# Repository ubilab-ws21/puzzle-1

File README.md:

# Divert power to machine room door (puzzle-1)
This puzzle is the first part of the 2021 ESCLAB.
According to that orange american man that once was US president, it's the best puzzle the world has ever seen.

## Objective
Divert the emergency power to the door that prevents you fom entering the second room.

## Story
There is some wiring on the wall. When you'll find some more panels to create the connection maybe you can divert the power to the door. Apparently the emergency power has not been used in ages.  
  
You spot a cube on the table in the room thats sides look like panels that yould be used for that.  
  
Upon further inspection you see that the cube starts sparkling when moving it in the hand. Also there are weird symbols on each side.  
Also in the room there is some kind of comic, that has the symbols in the title and a hint "to the sun".  
Maybe placing the cube with the symbols of the comic towards the sun (top) in the correct order it will open.

After finishing the sequence the cube lights up greeen and suddenly the panels will unlatch so you can take 'em off.  
You solve the wire-maze, given by the panels and place them so the connection between "emergency power" and the keypad is created on the wall.  

The door opens and you step into the next room.

And then you die. Or maybe something nicer happens - that's up to the people doing the next puzzles. :)

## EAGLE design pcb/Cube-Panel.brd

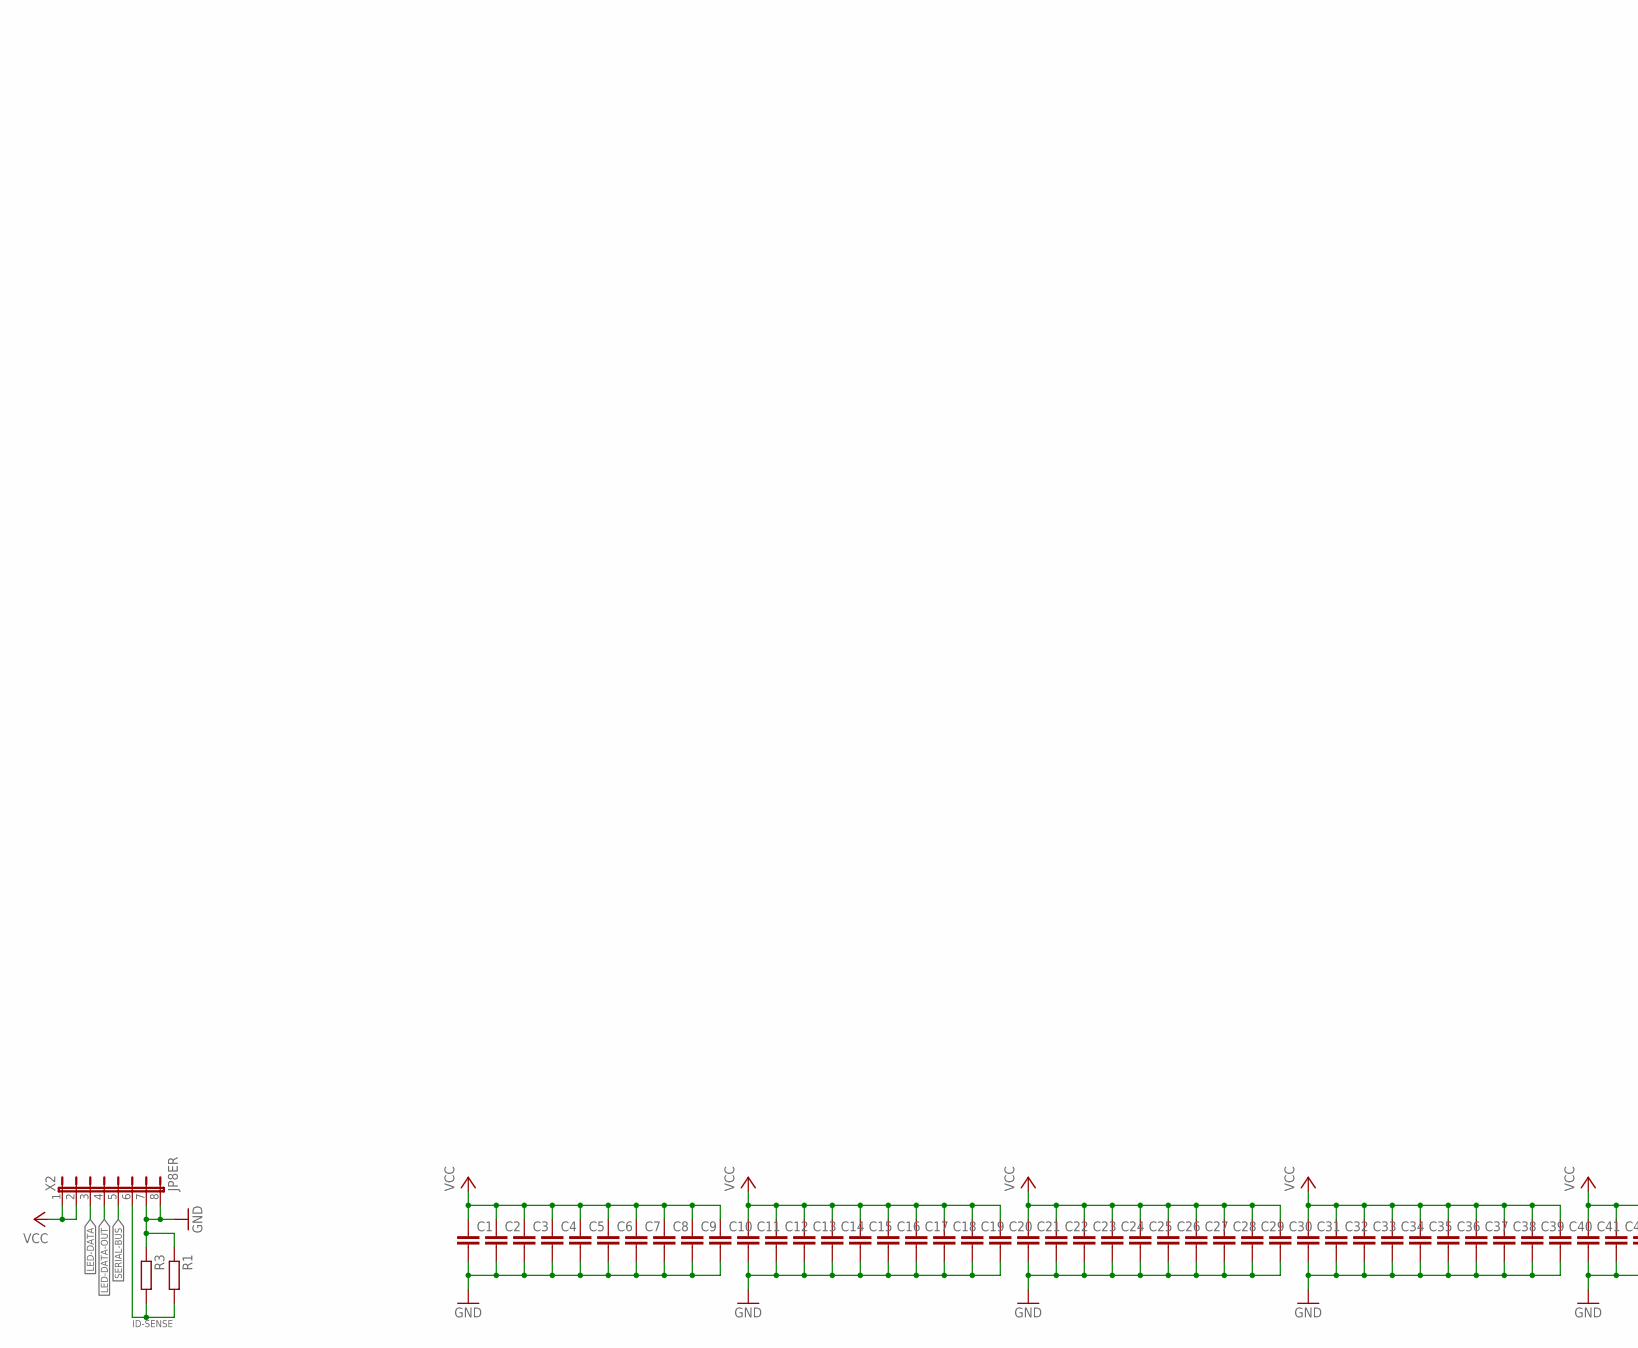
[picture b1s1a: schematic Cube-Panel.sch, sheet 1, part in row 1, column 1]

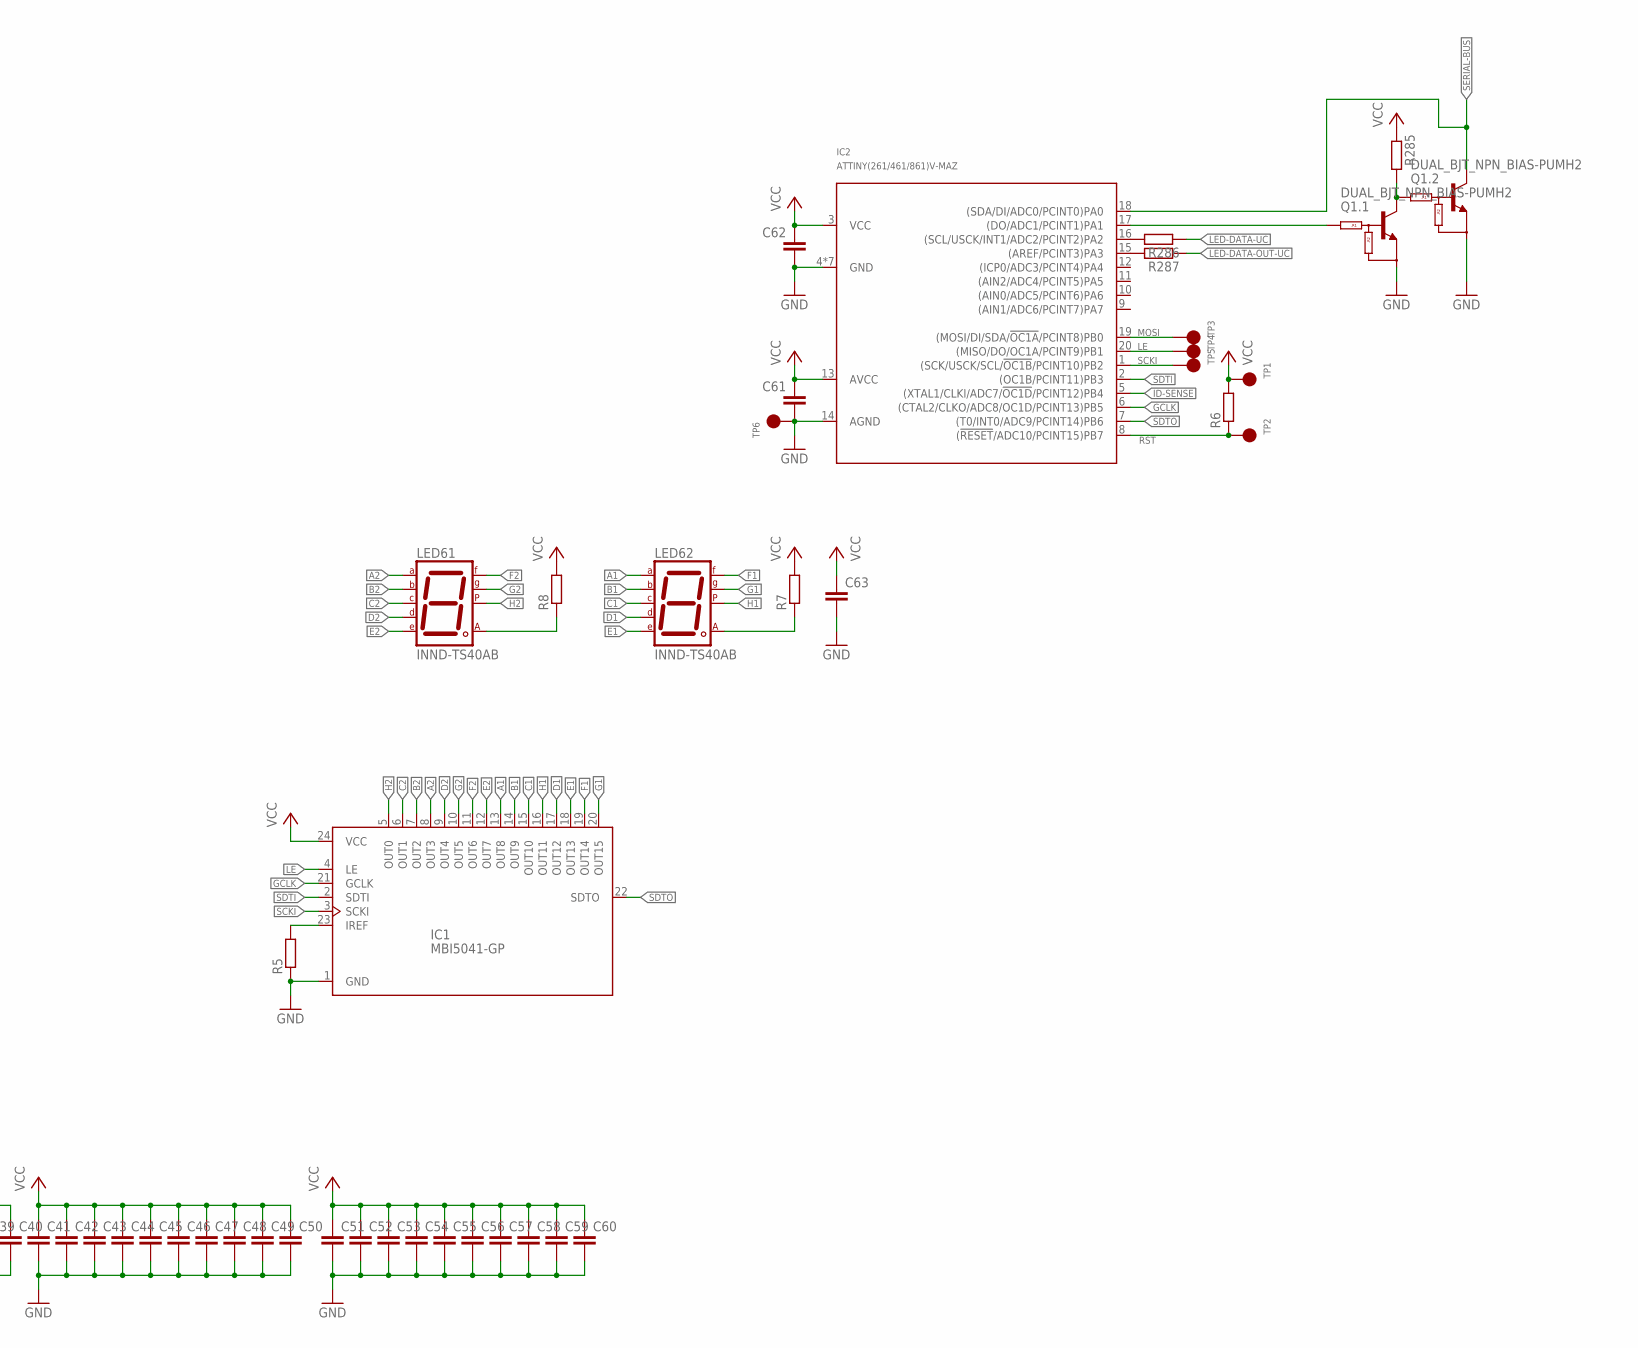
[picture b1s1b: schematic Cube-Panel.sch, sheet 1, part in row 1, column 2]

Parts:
C1, C2, C3, C4, C5, C6, C7, C8, C9, C10, C11, C12, C13, C14, C15, C16, C17, C18, C19, C20, C21, C22, C23, C24, C25, C26, C27, C28, C29, C30, C31, C32, C33, C34, C35, C36, C37, C38, C39, C40, C41, C42, C43, C44, C45, C46, C47, C48, C49, C50, C51, C52, C53, C54, C55, C56, C57, C58, C59, C60, C61, C62, C63: KONDENSATOR-0603; 0603
IC1: MBI5041-GP; SSOP24-150-0.635
IC2: ATTINY(261/461/861)V-MAZ; QFN-20
LED61, LED62: INND-TS40AB; 7SEG-13
Q1: DUAL_BJT_NPN_BIAS-PUMH2; SOT-363(SC-88)
R1, R3, R5, R6, R7, R8, R285, R286, R287: WIDERSTAND-0603; 0603
TP1, TP2, TP3, TP4, TP5, TP6: TP; TP[1.5][R]
X2: JP8ER; JP8

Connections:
A1: IC1.13 (OUT8), LED62.10 (A)
A2: IC1.8 (OUT3), LED61.10 (A)
B1: IC1.14 (OUT9), LED62.9 (B)
B2: IC1.7 (OUT2), LED61.9 (B)
C1: IC1.15 (OUT10), LED62.8 (C)
C2: IC1.6 (OUT1), LED61.8 (C)
D1: IC1.17 (OUT12), LED62.5 (D)
D2: IC1.9 (OUT4), LED61.5 (D)
E1: IC1.18 (OUT13), LED62.1 (E)
E2: IC1.12 (OUT7), LED61.1 (E)
F1: IC1.19 (OUT14), LED62.2 (F)
F2: IC1.11 (OUT6), LED61.2 (F)
G1: IC1.20 (OUT15), LED62.3 (G)
G2: IC1.10 (OUT5), LED61.3 (G)
GCLK: IC1.21 (GCLK), IC2.6 ((CTAL2/CLKO/ADC8/OC1D/PCINT13)PB5)
GND: C1.P$2 (2), C2.P$2 (2), C3.P$2 (2), C4.P$2 (2), C5.P$2 (2), C6.P$2 (2), C7.P$2 (2), C8.P$2 (2), C9.P$2 (2), C10.P$2 (2), C11.P$2 (2), C12.P$2 (2), C13.P$2 (2), C14.P$2 (2), C15.P$2 (2), C16.P$2 (2), C17.P$2 (2), C18.P$2 (2), C19.P$2 (2), C20.P$2 (2), C21.P$2 (2), C22.P$2 (2), C23.P$2 (2), C24.P$2 (2), C25.P$2 (2), C26.P$2 (2), C27.P$2 (2), C28.P$2 (2), C29.P$2 (2), C30.P$2 (2), C31.P$2 (2), C32.P$2 (2), C33.P$2 (2), C34.P$2 (2), C35.P$2 (2), C36.P$2 (2), C37.P$2 (2), C38.P$2 (2), C39.P$2 (2), C40.P$2 (2), C41.P$2 (2), C42.P$2 (2), C43.P$2 (2), C44.P$2 (2), C45.P$2 (2), C46.P$2 (2), C47.P$2 (2), C48.P$2 (2), C49.P$2 (2), C50.P$2 (2), C51.P$2 (2), C52.P$2 (2), C53.P$2 (2), C54.P$2 (2), C55.P$2 (2), C56.P$2 (2), C57.P$2 (2), C58.P$2 (2), C59.P$2 (2), C60.P$2 (2), C61.P$2 (2), C62.P$2 (2), C63.P$2 (2), IC1.1 (GND), IC2.4 (GND), IC2.14 (AGND), IC2.PAD (GND), IC2.PAD$1 (GND), IC2.PAD$2 (GND), IC2.PAD$3 (GND), IC2.PAD$4 (GND), IC2.PAD$5 (GND), Q1.1 (E), Q1.4 (E), R1.P$1 (1), R3.P$1 (1), R5.P$1 (1), TP6.P$1, X2.7, X2.8; also elsewhere on the board
H1: IC1.16 (OUT11), LED62.7 (DP)
H2: IC1.5 (OUT0), LED61.7 (DP)
ID-SENSE: IC2.5 ((XTAL1/CLKI/ADC7/!OC1D!/PCINT12)PB4), R1.P$2 (2), R3.P$2 (2), X2.6
LE: IC1.4 (LE), IC2.20 ((MISO/DO/OC1A/PCINT9)PB1), TP4.P$1
LED-DATA: X2.3; also elsewhere on the board
LED-DATA-OUT: X2.4; also elsewhere on the board
LED-DATA-OUT-UC: R287.P$1 (1); also elsewhere on the board
LED-DATA-UC: R286.P$1 (1); also elsewhere on the board
MOSI: IC2.19 ((MOSI/DI/SDA/!OC1A!/PCINT8)PB0), TP3.P$1
unnamed: IC1.23 (IREF), R5.P$2 (2)
unnamed: IC2.16 ((SCL/USCK/INT1/ADC2/PCINT2)PA2), R286.P$2 (2)
unnamed: Q1.5 (B), Q1.6 (C), R285.P$2 (2)
unnamed: IC2.15 ((AREF/PCINT3)PA3), R287.P$2 (2)
unnamed: LED61.6 (CA2), R8.P$1 (1)
unnamed: LED62.6 (CA2), R7.P$1 (1)
RST: IC2.8 ((!RESET!/ADC10/PCINT15)PB7), R6.P$1 (1), TP2.P$1
SCKI: IC1.3 (SCKI), IC2.1 ((SCK/USCK/SCL/!OC1B!/PCINT10)PB2), TP5.P$1
SDTI: IC1.2 (SDTI), IC2.2 ((OC1B/PCINT11)PB3)
SDTO: IC1.22 (SDTO), IC2.7 ((T0/INT0/ADC9/PCINT14)PB6)
SERIAL-BUS: IC2.18 ((SDA/DI/ADC0/PCINT0)PA0), Q1.3 (C), X2.5
SERIAL-BUS-TX: IC2.17 ((DO/ADC1/PCINT1)PA1), Q1.2 (B)
VCC: C1.P$1 (1), C2.P$1 (1), C3.P$1 (1), C4.P$1 (1), C5.P$1 (1), C6.P$1 (1), C7.P$1 (1), C8.P$1 (1), C9.P$1 (1), C10.P$1 (1), C11.P$1 (1), C12.P$1 (1), C13.P$1 (1), C14.P$1 (1), C15.P$1 (1), C16.P$1 (1), C17.P$1 (1), C18.P$1 (1), C19.P$1 (1), C20.P$1 (1), C21.P$1 (1), C22.P$1 (1), C23.P$1 (1), C24.P$1 (1), C25.P$1 (1), C26.P$1 (1), C27.P$1 (1), C28.P$1 (1), C29.P$1 (1), C30.P$1 (1), C31.P$1 (1), C32.P$1 (1), C33.P$1 (1), C34.P$1 (1), C35.P$1 (1), C36.P$1 (1), C37.P$1 (1), C38.P$1 (1), C39.P$1 (1), C40.P$1 (1), C41.P$1 (1), C42.P$1 (1), C43.P$1 (1), C44.P$1 (1), C45.P$1 (1), C46.P$1 (1), C47.P$1 (1), C48.P$1 (1), C49.P$1 (1), C50.P$1 (1), C51.P$1 (1), C52.P$1 (1), C53.P$1 (1), C54.P$1 (1), C55.P$1 (1), C56.P$1 (1), C57.P$1 (1), C58.P$1 (1), C59.P$1 (1), C60.P$1 (1), C61.P$1 (1), C62.P$1 (1), C63.P$1 (1), IC1.24 (VCC), IC2.3 (VCC), IC2.13 (AVCC), R6.P$2 (2), R7.P$2 (2), R8.P$2 (2), R285.P$1 (1), TP1.P$1, X2.1, X2.2; also elsewhere on the board

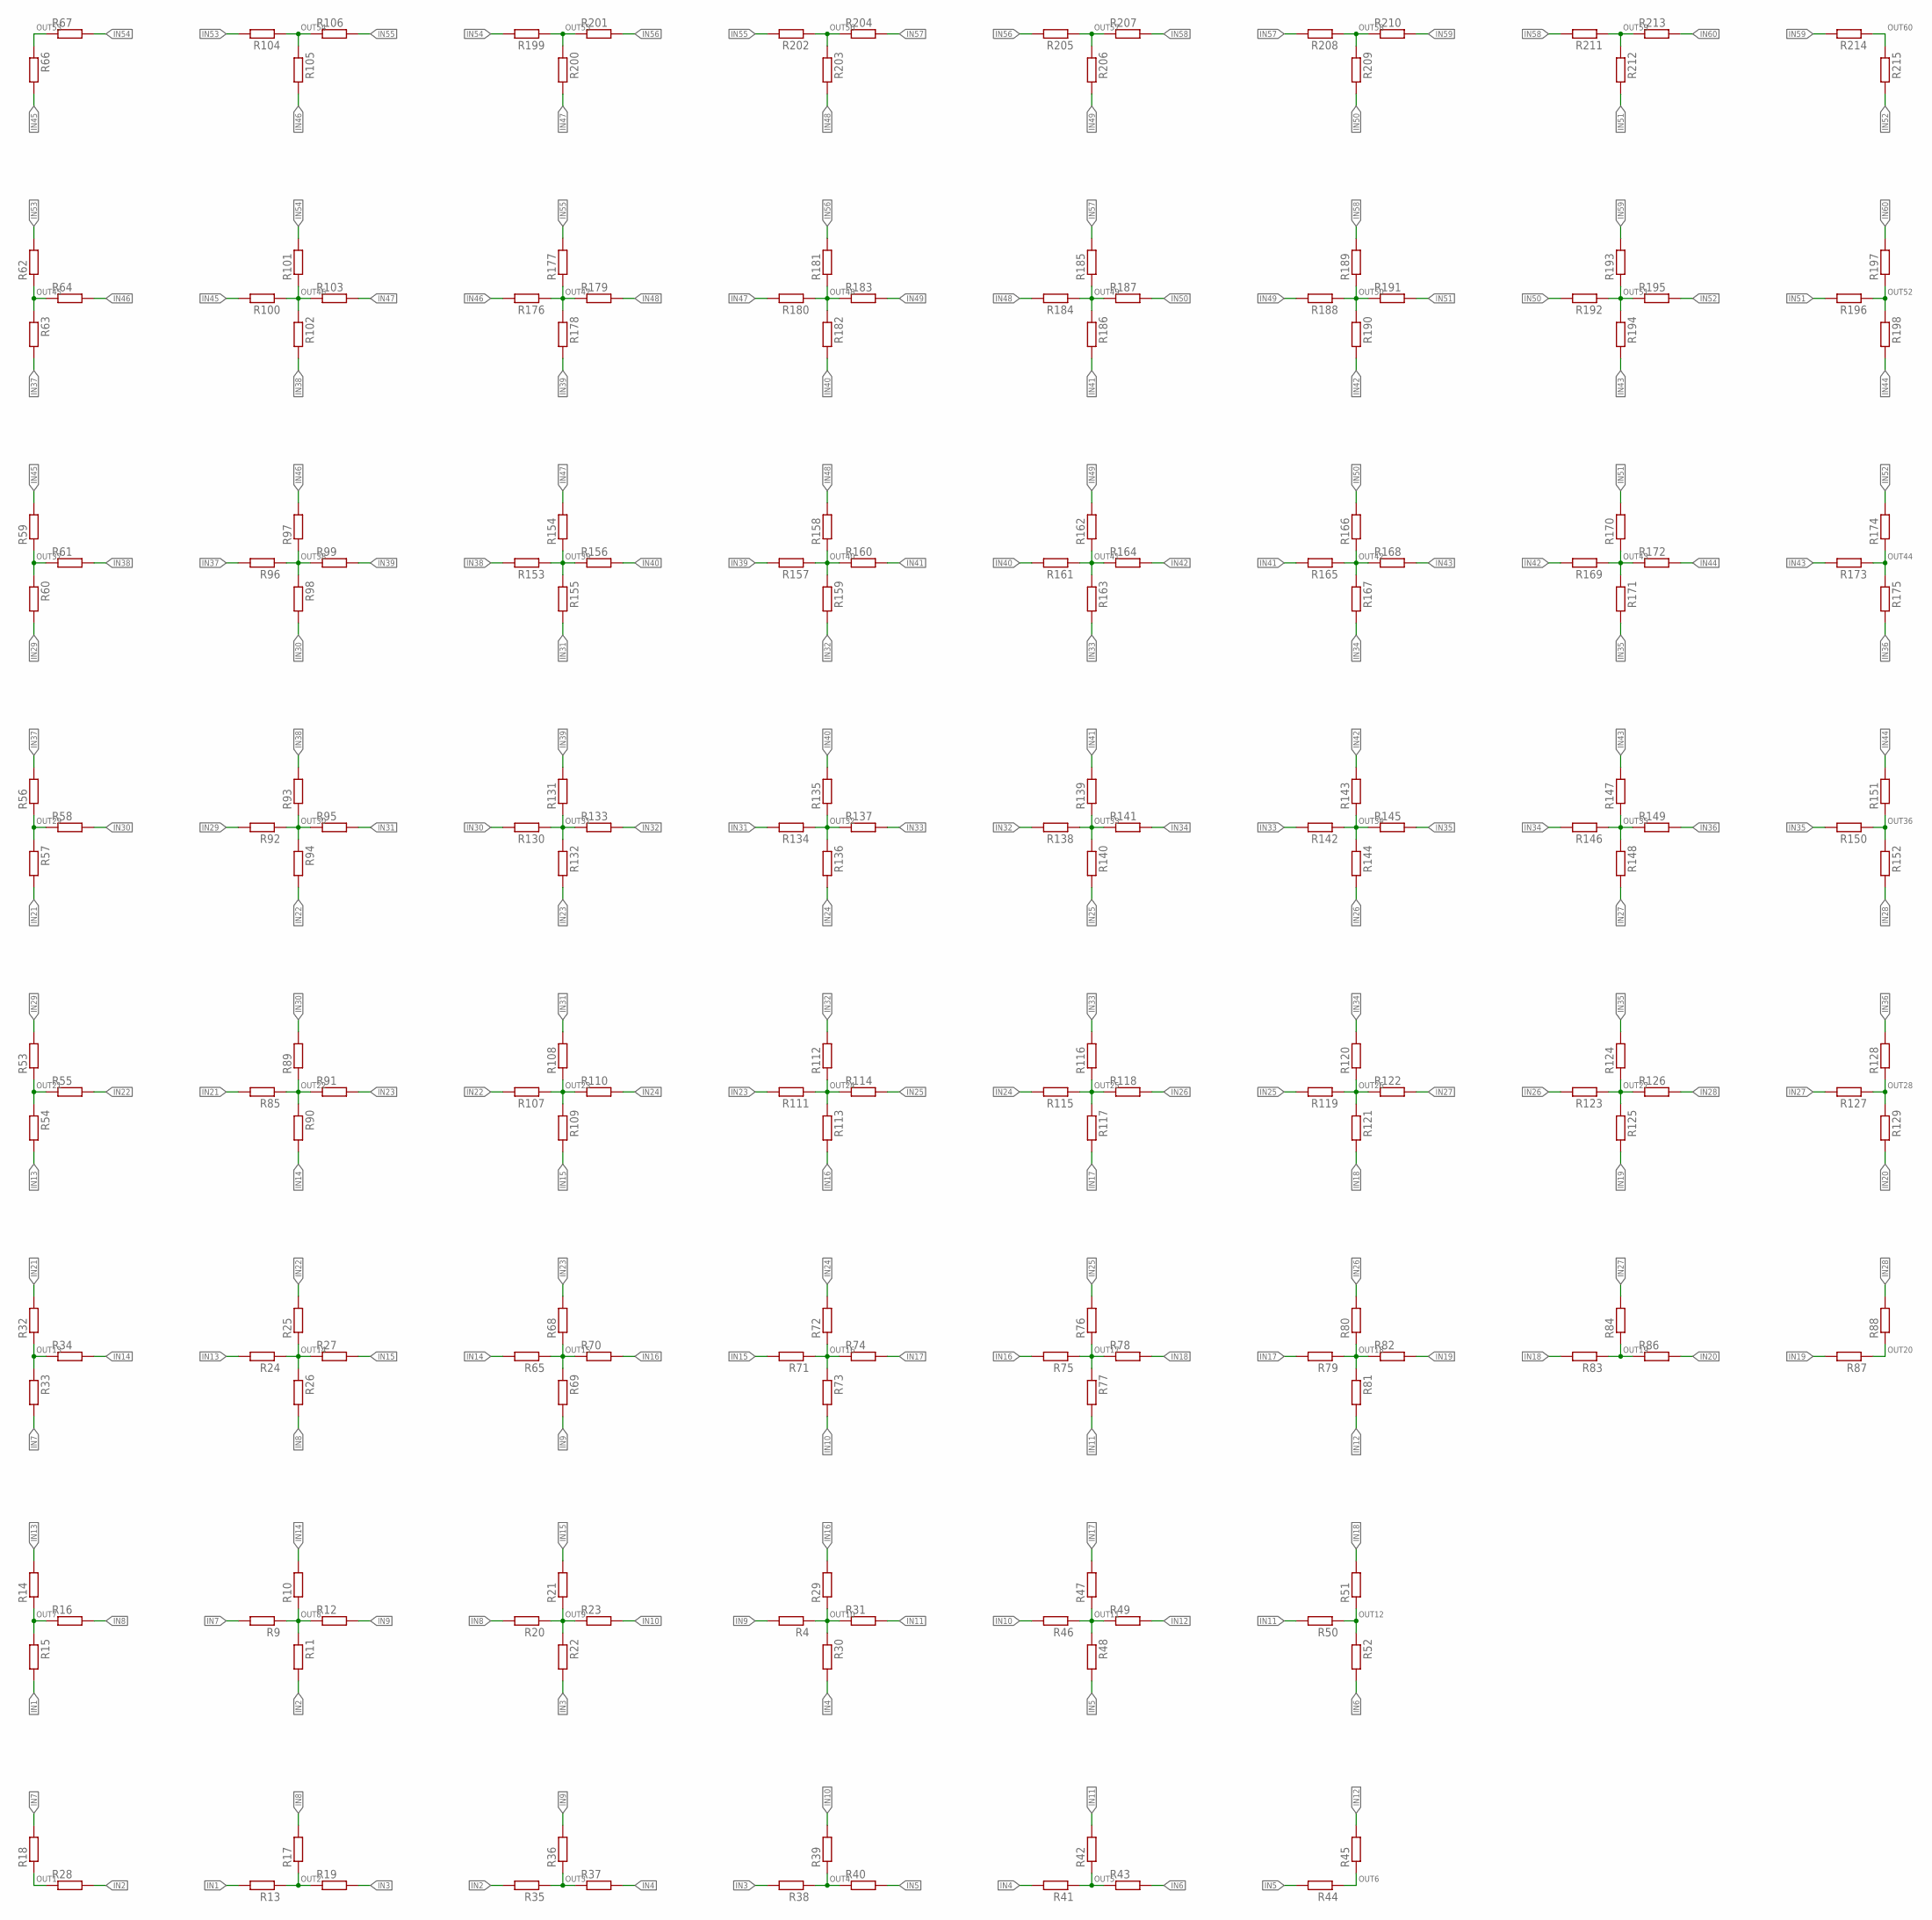
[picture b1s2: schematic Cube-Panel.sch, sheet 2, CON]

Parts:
R4, R9, R10, R11, R12, R13, R14, R15, R16, R17, R18, R19, R20, R21, R22, R23, R24, R25, R26, R27, R28, R29, R30, R31, R32, R33, R34, R35, R36, R37, R38, R39, R40, R41, R42, R43, R44, R45, R46, R47, R48, R49, R50, R51, R52, R53, R54, R55, R56, R57, R58, R59, R60, R61, R62, R63, R64, R65, R66, R67, R68, R69, R70, R71, R72, R73, R74, R75, R76, R77, R78, R79, R80, R81, R82, R83, R84, R85, R86, R87, R88, R89, R90, R91, R92, R93, R94, R95, R96, R97, R98, R99, R100, R101, R102, R103, R104, R105, R106, R107, R108, R109, R110, R111, R112, R113, R114, R115, R116, R117, R118, R119, R120, R121, R122, R123, R124, R125, R126, R127, R128, R129, R130, R131, R132, R133, R134, R135, R136, R137, R138, R139, R140, R141, R142, R143, R144, R145, R146, R147, R148, R149, R150, R151, R152, R153, R154, R155, R156, R157, R158, R159, R160, R161, R162, R163, R164, R165, R166, R167, R168, R169, R170, R171, R172, R173, R174, R175, R176, R177, R178, R179, R180, R181, R182, R183, R184, R185, R186, R187, R188, R189, R190, R191, R192, R193, R194, R195, R196, R197, R198, R199, R200, R201, R202, R203, R204, R205, R206, R207, R208, R209, R210, R211, R212, R213, R214, R215: WIDERSTAND-0603; 0603

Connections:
IN1: R13.P$2 (2), R15.P$2 (2); also elsewhere on the board
IN2: R11.P$2 (2), R28.P$2 (2), R35.P$2 (2); also elsewhere on the board
IN3: R19.P$2 (2), R22.P$2 (2), R38.P$2 (2); also elsewhere on the board
IN4: R30.P$2 (2), R37.P$2 (2), R41.P$2 (2); also elsewhere on the board
IN5: R40.P$2 (2), R44.P$2 (2), R48.P$2 (2); also elsewhere on the board
IN6: R43.P$2 (2), R52.P$2 (2); also elsewhere on the board
IN7: R9.P$2 (2), R18.P$2 (2), R33.P$2 (2); also elsewhere on the board
IN8: R16.P$2 (2), R17.P$2 (2), R20.P$2 (2), R26.P$2 (2); also elsewhere on the board
IN9: R4.P$2 (2), R12.P$2 (2), R36.P$2 (2), R69.P$2 (2); also elsewhere on the board
IN10: R23.P$2 (2), R39.P$2 (2), R46.P$2 (2), R73.P$2 (2); also elsewhere on the board
IN11: R31.P$2 (2), R42.P$2 (2), R50.P$2 (2), R77.P$2 (2); also elsewhere on the board
IN12: R45.P$2 (2), R49.P$2 (2), R81.P$2 (2); also elsewhere on the board
IN13: R14.P$2 (2), R24.P$2 (2), R54.P$2 (2); also elsewhere on the board
IN14: R10.P$2 (2), R34.P$2 (2), R65.P$2 (2), R90.P$2 (2); also elsewhere on the board
IN15: R21.P$2 (2), R27.P$2 (2), R71.P$2 (2), R109.P$2 (2); also elsewhere on the board
IN16: R29.P$2 (2), R70.P$2 (2), R75.P$2 (2), R113.P$2 (2); also elsewhere on the board
IN17: R47.P$2 (2), R74.P$2 (2), R79.P$2 (2), R117.P$2 (2); also elsewhere on the board
IN18: R51.P$2 (2), R78.P$2 (2), R83.P$2 (2), R121.P$2 (2); also elsewhere on the board
IN19: R82.P$2 (2), R87.P$2 (2), R125.P$2 (2); also elsewhere on the board
IN20: R86.P$2 (2), R129.P$2 (2); also elsewhere on the board
IN21: R32.P$2 (2), R57.P$2 (2), R85.P$2 (2); also elsewhere on the board
IN22: R25.P$2 (2), R55.P$2 (2), R94.P$2 (2), R107.P$2 (2); also elsewhere on the board
IN23: R68.P$2 (2), R91.P$2 (2), R111.P$2 (2), R132.P$2 (2); also elsewhere on the board
IN24: R72.P$2 (2), R110.P$2 (2), R115.P$2 (2), R136.P$2 (2); also elsewhere on the board
IN25: R76.P$2 (2), R114.P$2 (2), R119.P$2 (2), R140.P$2 (2); also elsewhere on the board
IN26: R80.P$2 (2), R118.P$2 (2), R123.P$2 (2), R144.P$2 (2); also elsewhere on the board
IN27: R84.P$2 (2), R122.P$2 (2), R127.P$2 (2), R148.P$2 (2); also elsewhere on the board
IN28: R88.P$2 (2), R126.P$2 (2), R152.P$2 (2); also elsewhere on the board
IN29: R53.P$2 (2), R60.P$2 (2), R92.P$2 (2); also elsewhere on the board
IN30: R58.P$2 (2), R89.P$2 (2), R98.P$2 (2), R130.P$2 (2); also elsewhere on the board
IN31: R95.P$2 (2), R108.P$2 (2), R134.P$2 (2), R155.P$2 (2); also elsewhere on the board
IN32: R112.P$2 (2), R133.P$2 (2), R138.P$2 (2), R159.P$2 (2); also elsewhere on the board
IN33: R116.P$2 (2), R137.P$2 (2), R142.P$2 (2), R163.P$2 (2); also elsewhere on the board
IN34: R120.P$2 (2), R141.P$2 (2), R146.P$2 (2), R167.P$2 (2); also elsewhere on the board
IN35: R124.P$2 (2), R145.P$2 (2), R150.P$2 (2), R171.P$2 (2); also elsewhere on the board
IN36: R128.P$2 (2), R149.P$2 (2), R175.P$2 (2); also elsewhere on the board
IN37: R56.P$2 (2), R63.P$2 (2), R96.P$2 (2); also elsewhere on the board
IN38: R61.P$2 (2), R93.P$2 (2), R102.P$2 (2), R153.P$2 (2); also elsewhere on the board
IN39: R99.P$2 (2), R131.P$2 (2), R157.P$2 (2), R178.P$2 (2); also elsewhere on the board
IN40: R135.P$2 (2), R156.P$2 (2), R161.P$2 (2), R182.P$2 (2); also elsewhere on the board
IN41: R139.P$2 (2), R160.P$2 (2), R165.P$2 (2), R186.P$2 (2); also elsewhere on the board
IN42: R143.P$2 (2), R164.P$2 (2), R169.P$2 (2), R190.P$2 (2); also elsewhere on the board
IN43: R147.P$2 (2), R168.P$2 (2), R173.P$2 (2), R194.P$2 (2); also elsewhere on the board
IN44: R151.P$2 (2), R172.P$2 (2), R198.P$2 (2); also elsewhere on the board
IN45: R59.P$2 (2), R66.P$2 (2), R100.P$2 (2); also elsewhere on the board
IN46: R64.P$2 (2), R97.P$2 (2), R105.P$2 (2), R176.P$2 (2); also elsewhere on the board
IN47: R103.P$2 (2), R154.P$2 (2), R180.P$2 (2), R200.P$2 (2); also elsewhere on the board
IN48: R158.P$2 (2), R179.P$2 (2), R184.P$2 (2), R203.P$2 (2); also elsewhere on the board
IN49: R162.P$2 (2), R183.P$2 (2), R188.P$2 (2), R206.P$2 (2); also elsewhere on the board
IN50: R166.P$2 (2), R187.P$2 (2), R192.P$2 (2), R209.P$2 (2); also elsewhere on the board
IN51: R170.P$2 (2), R191.P$2 (2), R196.P$2 (2), R212.P$2 (2); also elsewhere on the board
IN52: R174.P$2 (2), R195.P$2 (2), R215.P$2 (2); also elsewhere on the board
IN53: R62.P$2 (2), R104.P$2 (2); also elsewhere on the board
IN54: R67.P$2 (2), R101.P$2 (2), R199.P$2 (2); also elsewhere on the board
IN55: R106.P$2 (2), R177.P$2 (2), R202.P$2 (2); also elsewhere on the board
IN56: R181.P$2 (2), R201.P$2 (2), R205.P$2 (2); also elsewhere on the board
IN57: R185.P$2 (2), R204.P$2 (2), R208.P$2 (2); also elsewhere on the board
IN58: R189.P$2 (2), R207.P$2 (2), R211.P$2 (2); also elsewhere on the board
IN59: R193.P$2 (2), R210.P$2 (2), R214.P$2 (2); also elsewhere on the board
IN60: R197.P$2 (2), R213.P$2 (2); also elsewhere on the board
OUT1: R18.P$1 (1), R28.P$1 (1); also elsewhere on the board
OUT2: R13.P$1 (1), R17.P$1 (1), R19.P$1 (1); also elsewhere on the board
OUT3: R35.P$1 (1), R36.P$1 (1), R37.P$1 (1); also elsewhere on the board
OUT4: R38.P$1 (1), R39.P$1 (1), R40.P$1 (1); also elsewhere on the board
OUT5: R41.P$1 (1), R42.P$1 (1), R43.P$1 (1); also elsewhere on the board
OUT6: R44.P$1 (1), R45.P$1 (1); also elsewhere on the board
OUT7: R14.P$1 (1), R15.P$1 (1), R16.P$1 (1); also elsewhere on the board
OUT8: R9.P$1 (1), R10.P$1 (1), R11.P$1 (1), R12.P$1 (1); also elsewhere on the board
OUT9: R20.P$1 (1), R21.P$1 (1), R22.P$1 (1), R23.P$1 (1); also elsewhere on the board
OUT10: R4.P$1 (1), R29.P$1 (1), R30.P$1 (1), R31.P$1 (1); also elsewhere on the board
OUT11: R46.P$1 (1), R47.P$1 (1), R48.P$1 (1), R49.P$1 (1); also elsewhere on the board
OUT12: R50.P$1 (1), R51.P$1 (1), R52.P$1 (1); also elsewhere on the board
OUT13: R32.P$1 (1), R33.P$1 (1), R34.P$1 (1); also elsewhere on the board
OUT14: R24.P$1 (1), R25.P$1 (1), R26.P$1 (1), R27.P$1 (1); also elsewhere on the board
OUT15: R65.P$1 (1), R68.P$1 (1), R69.P$1 (1), R70.P$1 (1); also elsewhere on the board
OUT16: R71.P$1 (1), R72.P$1 (1), R73.P$1 (1), R74.P$1 (1); also elsewhere on the board
OUT17: R75.P$1 (1), R76.P$1 (1), R77.P$1 (1), R78.P$1 (1); also elsewhere on the board
OUT18: R79.P$1 (1), R80.P$1 (1), R81.P$1 (1), R82.P$1 (1); also elsewhere on the board
OUT19: R83.P$1 (1), R84.P$1 (1), R86.P$1 (1); also elsewhere on the board
OUT20: R87.P$1 (1), R88.P$1 (1); also elsewhere on the board
OUT21: R53.P$1 (1), R54.P$1 (1), R55.P$1 (1); also elsewhere on the board
OUT22: R85.P$1 (1), R89.P$1 (1), R90.P$1 (1), R91.P$1 (1); also elsewhere on the board
OUT23: R107.P$1 (1), R108.P$1 (1), R109.P$1 (1), R110.P$1 (1); also elsewhere on the board
OUT24: R111.P$1 (1), R112.P$1 (1), R113.P$1 (1), R114.P$1 (1); also elsewhere on the board
OUT25: R115.P$1 (1), R116.P$1 (1), R117.P$1 (1), R118.P$1 (1); also elsewhere on the board
OUT26: R119.P$1 (1), R120.P$1 (1), R121.P$1 (1), R122.P$1 (1); also elsewhere on the board
OUT27: R123.P$1 (1), R124.P$1 (1), R125.P$1 (1), R126.P$1 (1); also elsewhere on the board
OUT28: R127.P$1 (1), R128.P$1 (1), R129.P$1 (1); also elsewhere on the board
OUT29: R56.P$1 (1), R57.P$1 (1), R58.P$1 (1); also elsewhere on the board
OUT30: R92.P$1 (1), R93.P$1 (1), R94.P$1 (1), R95.P$1 (1); also elsewhere on the board
OUT31: R130.P$1 (1), R131.P$1 (1), R132.P$1 (1), R133.P$1 (1); also elsewhere on the board
OUT32: R134.P$1 (1), R135.P$1 (1), R136.P$1 (1), R137.P$1 (1); also elsewhere on the board
OUT33: R138.P$1 (1), R139.P$1 (1), R140.P$1 (1), R141.P$1 (1); also elsewhere on the board
OUT34: R142.P$1 (1), R143.P$1 (1), R144.P$1 (1), R145.P$1 (1); also elsewhere on the board
OUT35: R146.P$1 (1), R147.P$1 (1), R148.P$1 (1), R149.P$1 (1); also elsewhere on the board
OUT36: R150.P$1 (1), R151.P$1 (1), R152.P$1 (1); also elsewhere on the board
OUT37: R59.P$1 (1), R60.P$1 (1), R61.P$1 (1); also elsewhere on the board
OUT38: R96.P$1 (1), R97.P$1 (1), R98.P$1 (1), R99.P$1 (1); also elsewhere on the board
OUT39: R153.P$1 (1), R154.P$1 (1), R155.P$1 (1), R156.P$1 (1); also elsewhere on the board
OUT40: R157.P$1 (1), R158.P$1 (1), R159.P$1 (1), R160.P$1 (1); also elsewhere on the board
OUT41: R161.P$1 (1), R162.P$1 (1), R163.P$1 (1), R164.P$1 (1); also elsewhere on the board
OUT42: R165.P$1 (1), R166.P$1 (1), R167.P$1 (1), R168.P$1 (1); also elsewhere on the board
OUT43: R169.P$1 (1), R170.P$1 (1), R171.P$1 (1), R172.P$1 (1); also elsewhere on the board
OUT44: R173.P$1 (1), R174.P$1 (1), R175.P$1 (1); also elsewhere on the board
OUT45: R62.P$1 (1), R63.P$1 (1), R64.P$1 (1); also elsewhere on the board
OUT46: R100.P$1 (1), R101.P$1 (1), R102.P$1 (1), R103.P$1 (1); also elsewhere on the board
OUT47: R176.P$1 (1), R177.P$1 (1), R178.P$1 (1), R179.P$1 (1); also elsewhere on the board
OUT48: R180.P$1 (1), R181.P$1 (1), R182.P$1 (1), R183.P$1 (1); also elsewhere on the board
OUT49: R184.P$1 (1), R185.P$1 (1), R186.P$1 (1), R187.P$1 (1); also elsewhere on the board
OUT50: R188.P$1 (1), R189.P$1 (1), R190.P$1 (1), R191.P$1 (1); also elsewhere on the board
OUT51: R192.P$1 (1), R193.P$1 (1), R194.P$1 (1), R195.P$1 (1); also elsewhere on the board
OUT52: R196.P$1 (1), R197.P$1 (1), R198.P$1 (1); also elsewhere on the board
OUT53: R66.P$1 (1), R67.P$1 (1); also elsewhere on the board
OUT54: R104.P$1 (1), R105.P$1 (1), R106.P$1 (1); also elsewhere on the board
OUT55: R199.P$1 (1), R200.P$1 (1), R201.P$1 (1); also elsewhere on the board
OUT56: R202.P$1 (1), R203.P$1 (1), R204.P$1 (1); also elsewhere on the board
OUT57: R205.P$1 (1), R206.P$1 (1), R207.P$1 (1); also elsewhere on the board
OUT58: R208.P$1 (1), R209.P$1 (1), R210.P$1 (1); also elsewhere on the board
OUT59: R211.P$1 (1), R212.P$1 (1), R213.P$1 (1); also elsewhere on the board
OUT60: R214.P$1 (1), R215.P$1 (1); also elsewhere on the board
